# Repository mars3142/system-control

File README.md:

# System Control

See the [wiki](https://wiki.mars3142.dev/project/maerklin/system_control/start) for more information.

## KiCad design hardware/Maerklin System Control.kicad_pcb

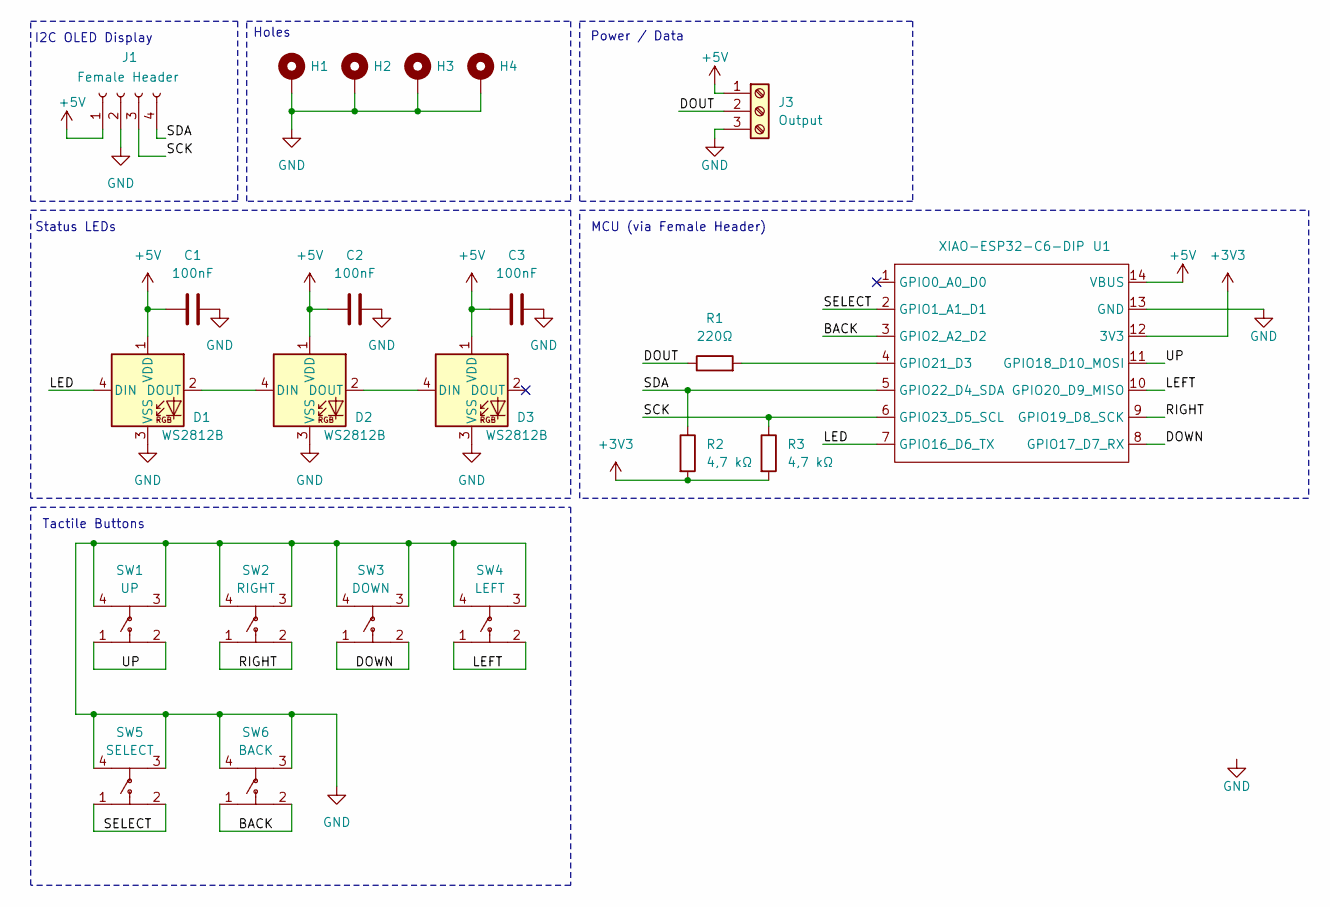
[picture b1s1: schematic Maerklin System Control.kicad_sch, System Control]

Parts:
C1, C2, C3: 100nF; C_0805_2012Metric_Pad1.18x1.45mm_HandSolder; LCSC C1711
D1, D2, D3: WS2812B; LED_WS2812B_PLCC4_5.0x5.0mm_P3.2mm; LCSC C22371521
H1: MH1; MountingHole_2.2mm_M2_Pad_Via
H2: MH2; MountingHole_2.2mm_M2_Pad_Via
H3: MH3; MountingHole_2.2mm_M2_Pad_Via
H4: MH4; MountingHole_2.2mm_M2_Pad_Via
J1: Female Header; PinSocket_1x04_P2.54mm_Horizontal; LCSC C5116530
J3: Output; TerminalBlock_Phoenix_MKDS-1,5-3_1x03_P5.00mm_Horizontal; LCSC Part C5188435
R1: 220Ω; R_0805_2012Metric_Pad1.20x1.40mm_HandSolder
R2, R3: 4,7 kΩ; R_0805_2012Metric_Pad1.20x1.40mm_HandSolder
SW1: UP; KEY-TH_4P-L6.0-W6.0-P3.90-LS7.8; LCSC Part C83205
SW2: RIGHT; KEY-TH_4P-L6.0-W6.0-P3.90-LS7.8; LCSC Part C83205
SW3: DOWN; KEY-TH_4P-L6.0-W6.0-P3.90-LS7.8; LCSC Part C83205
SW4: LEFT; KEY-TH_4P-L6.0-W6.0-P3.90-LS7.8; LCSC C83205
SW5: SELECT; KEY-TH_4P-L6.0-W6.0-P3.90-LS7.8; LCSC Part C83205
SW6: BACK; KEY-TH_4P-L6.0-W6.0-P3.90-LS7.8; LCSC Part C83205
U1: XIAO-ESP32-C6-DIP

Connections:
+3V3: R2.2, R3.2, U1.12 (3V3)
+5V: C1.1, C2.1, C3.1, D1.1 (VDD), D2.1 (VDD), D3.1 (VDD), J1.1, J3.1, U1.14 (VBUS)
/BACK: SW6.1, SW6.2, U1.3 (GPIO2_A2_D2)
/DOUT: J3.2, R1.1
/DOWN: SW3.1, SW3.2, U1.8 (GPIO17_D7_RX)
/LED: D1.4 (DIN), U1.7 (GPIO16_D6_TX)
/LEFT: SW4.1, SW4.2, U1.10 (GPIO20_D9_MISO)
/RIGHT: SW2.1, SW2.2, U1.9 (GPIO19_D8_SCK)
/SCK: J1.3, R3.1, U1.6 (GPIO23_D5_SCL)
/SDA: J1.4, R2.1, U1.5 (GPIO22_D4_SDA)
/SELECT: SW5.1, SW5.2, U1.2 (GPIO1_A1_D1)
/UP: SW1.1, SW1.2, U1.11 (GPIO18_D10_MOSI)
GND: C1.2, C2.2, C3.2, D1.3 (VSS), D2.3 (VSS), D3.3 (VSS), H1.1 (1_1), H2.1 (1_1), H3.1 (1_1), H4.1 (1_1), J1.2, J3.3, SW1.3, SW1.4, SW2.3, SW2.4, SW3.3, SW3.4, SW4.3, SW4.4, SW5.3, SW5.4, SW6.3, SW6.4, U1.13 (GND)
unnamed: D1.2 (DOUT), D2.4 (DIN)
unnamed: D2.2 (DOUT), D3.4 (DIN)
unnamed: R1.2, U1.4 (GPIO21_D3)

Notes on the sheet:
MCU (via Female Header)
Holes
Power / Data
Status LEDs
Tactile Buttons
I2C OLED Display

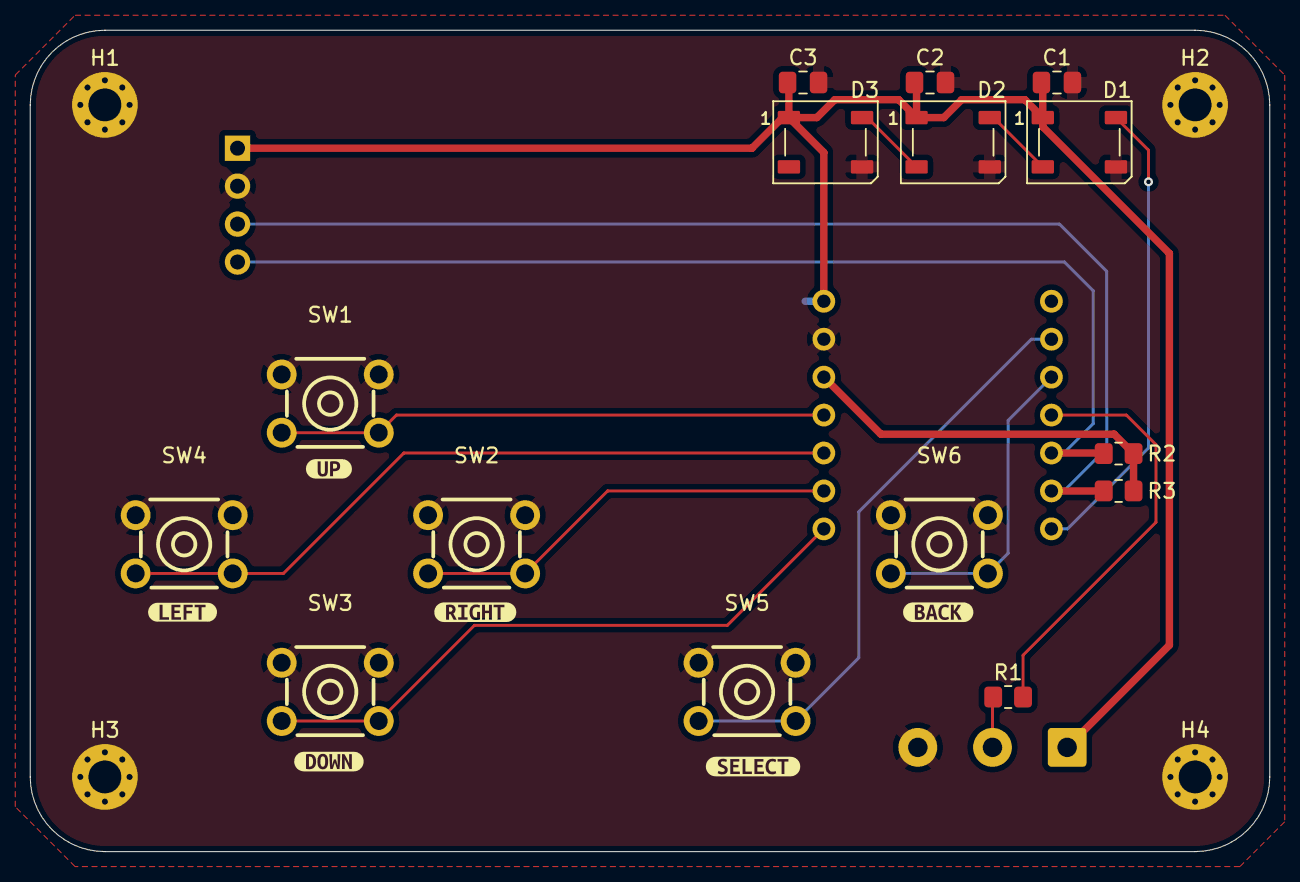
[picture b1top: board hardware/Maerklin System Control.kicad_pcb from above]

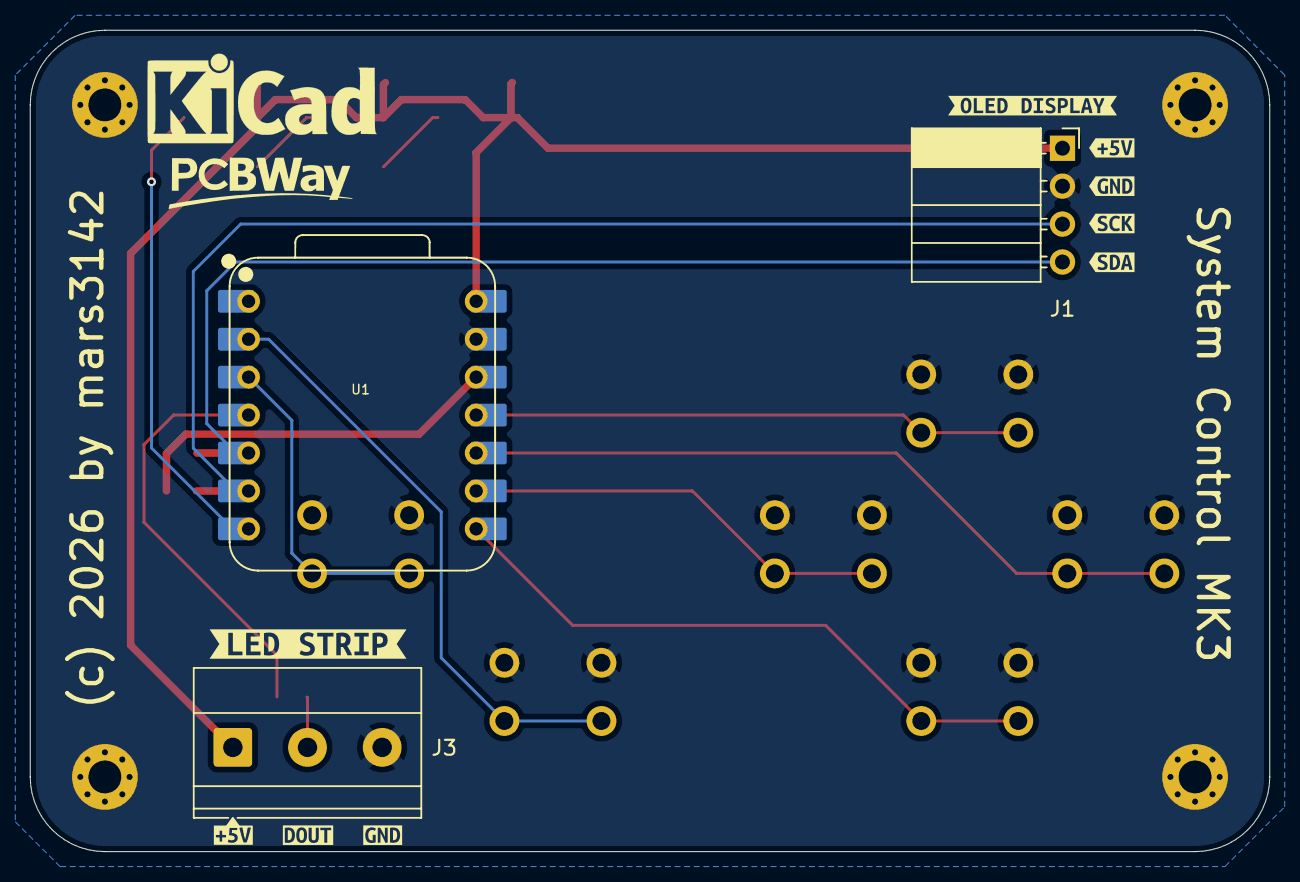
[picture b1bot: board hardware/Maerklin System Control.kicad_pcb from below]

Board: 2 copper layers, 83.0 x 55.0 mm, 37 parts (12 on the bottom side), 16 nets.

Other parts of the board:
kibuzzard-68D2E6D4: G***; kibuzzard-68D2E6D4
kibuzzard-68D2E6E4: G***; kibuzzard-68D2E6E4
kibuzzard-68D2E6EB: G***; kibuzzard-68D2E6EB
kibuzzard-68D2E6F2: G***; kibuzzard-68D2E6F2
kibuzzard-678A1323: G***; kibuzzard-678A1323
kibuzzard-6859B258: G***; kibuzzard-6859B258
kibuzzard-678980E8: G***; kibuzzard-678980E8
kibuzzard-678980F4: G***; kibuzzard-678980F4
kibuzzard-678981DB: G***; kibuzzard-678981DB
kibuzzard-678981FB: G***; kibuzzard-678981FB
kibuzzard-67898102: G***; kibuzzard-67898102
kibuzzard-67898208: G***; kibuzzard-67898208
kibuzzard-67898217: G***; kibuzzard-67898217
kibuzzard-67898221: G***; kibuzzard-67898221
kibuzzard-67898229: G***; kibuzzard-67898229

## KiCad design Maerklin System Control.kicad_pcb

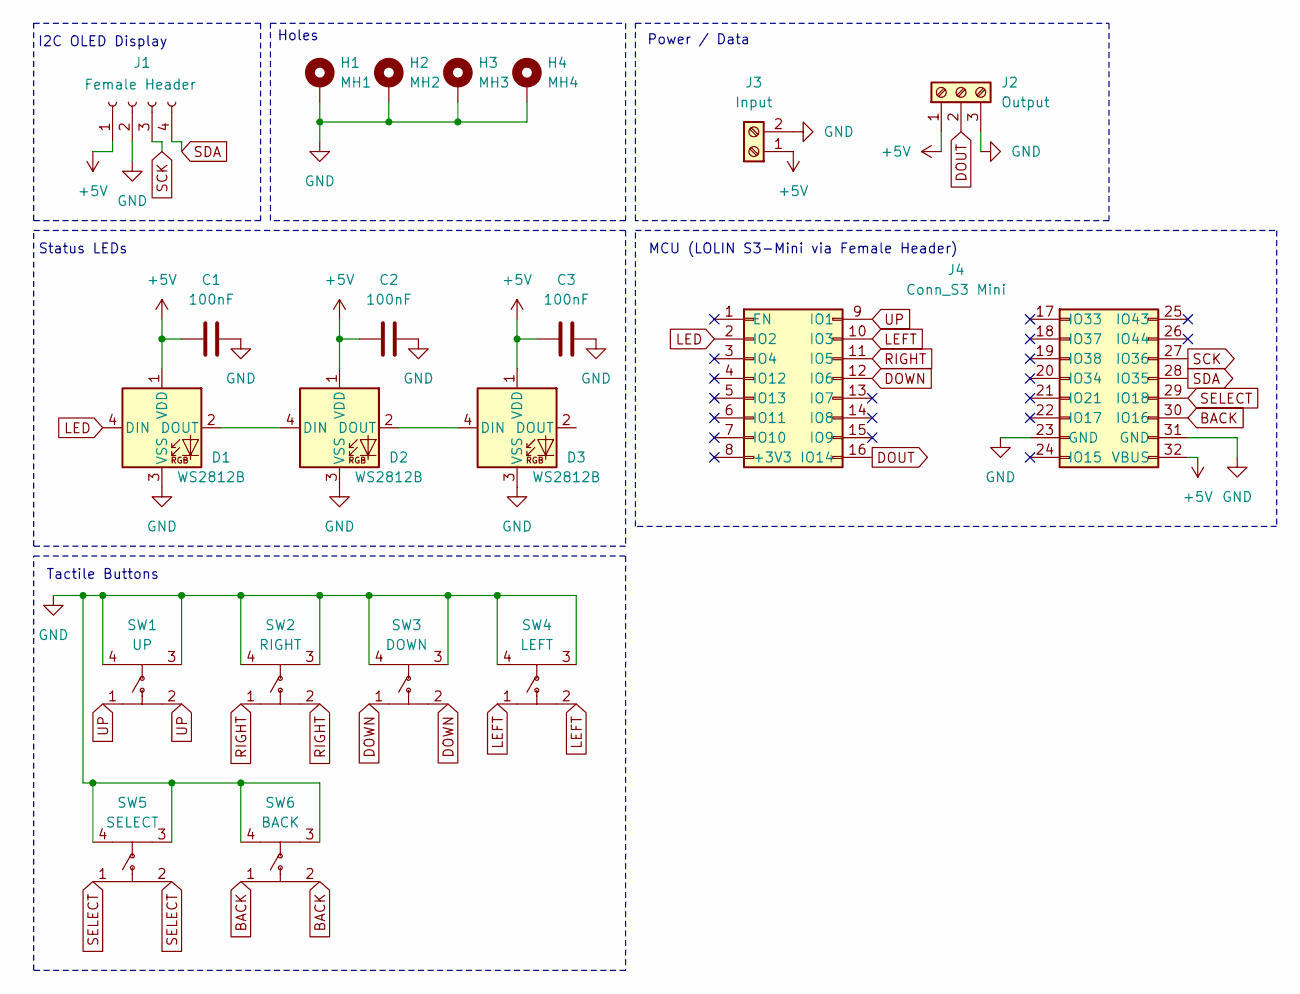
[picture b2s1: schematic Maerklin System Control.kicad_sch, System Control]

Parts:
C1, C2, C3: 100nF; C_0805_2012Metric_Pad1.18x1.45mm_HandSolder; LCSC C1711
D1, D2, D3: WS2812B; LED_WS2812B_PLCC4_5.0x5.0mm_P3.2mm; LCSC C22371521
H1: MH1; MountingHole_2.2mm_M2_Pad_Via
H2: MH2; MountingHole_2.2mm_M2_Pad_Via
H3: MH3; MountingHole_2.2mm_M2_Pad_Via
H4: MH4; MountingHole_2.2mm_M2_Pad_Via
J1: Female Header; PinSocket_1x04_P2.54mm_Vertical; LCSC C5116530
J2: Output; TerminalBlock_Phoenix_MKDS-1,5-3_1x03_P5.00mm_Horizontal; LCSC Part C5188435
J3: Input; TerminalBlock_Phoenix_MKDS-1,5-2_1x02_P5.00mm_Horizontal; LCSC Part C5188434
J4: Conn_S3 Mini; PinSocket_S3 Mini; LCSC Part C18722935
SW1: UP; KEY-TH_4P-L6.0-W6.0-P3.90-LS7.8; LCSC Part C83205
SW2: RIGHT; KEY-TH_4P-L6.0-W6.0-P3.90-LS7.8; LCSC Part C83205
SW3: DOWN; KEY-TH_4P-L6.0-W6.0-P3.90-LS7.8; LCSC Part C83205
SW4: LEFT; KEY-TH_4P-L6.0-W6.0-P3.90-LS7.8; LCSC C83205
SW5: SELECT; KEY-TH_4P-L6.0-W6.0-P3.90-LS7.8; LCSC Part C83205
SW6: BACK; KEY-TH_4P-L6.0-W6.0-P3.90-LS7.8; LCSC Part C83205

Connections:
+5V: C1.1, C2.1, C3.1, D1.1 (VDD), D2.1 (VDD), D3.1 (VDD), J1.1, J2.1, J3.1, J4.32 (VBUS)
BACK: J4.30 (IO16), SW6.1, SW6.2
DOUT: J2.2, J4.16 (IO14)
DOWN: J4.12 (IO6), SW3.1, SW3.2
GND: C1.2, C2.2, C3.2, D1.3 (VSS), D2.3 (VSS), D3.3 (VSS), H1.1, H2.1, H3.1, H4.1, J1.2, J2.3, J3.2, J4.23 (GND), J4.31 (GND), SW1.3, SW1.4, SW2.3, SW2.4, SW3.3, SW3.4, SW4.3, SW4.4, SW5.3, SW5.4, SW6.3, SW6.4
LED: D1.4 (DIN), J4.2 (IO2)
LEFT: J4.10 (IO3), SW4.1, SW4.2
unnamed: D1.2 (DOUT), D2.4 (DIN)
unnamed: D2.2 (DOUT), D3.4 (DIN)
RIGHT: J4.11 (IO5), SW2.1, SW2.2
SCK: J1.3, J4.27 (IO36)
SDA: J1.4, J4.28 (IO35)
SELECT: J4.29 (IO18), SW5.1, SW5.2
UP: J4.9 (IO1), SW1.1, SW1.2

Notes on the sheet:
MCU (LOLIN S3-Mini via Female Header)
Holes
Power / Data
Status LEDs
Tactile Buttons
I2C OLED Display

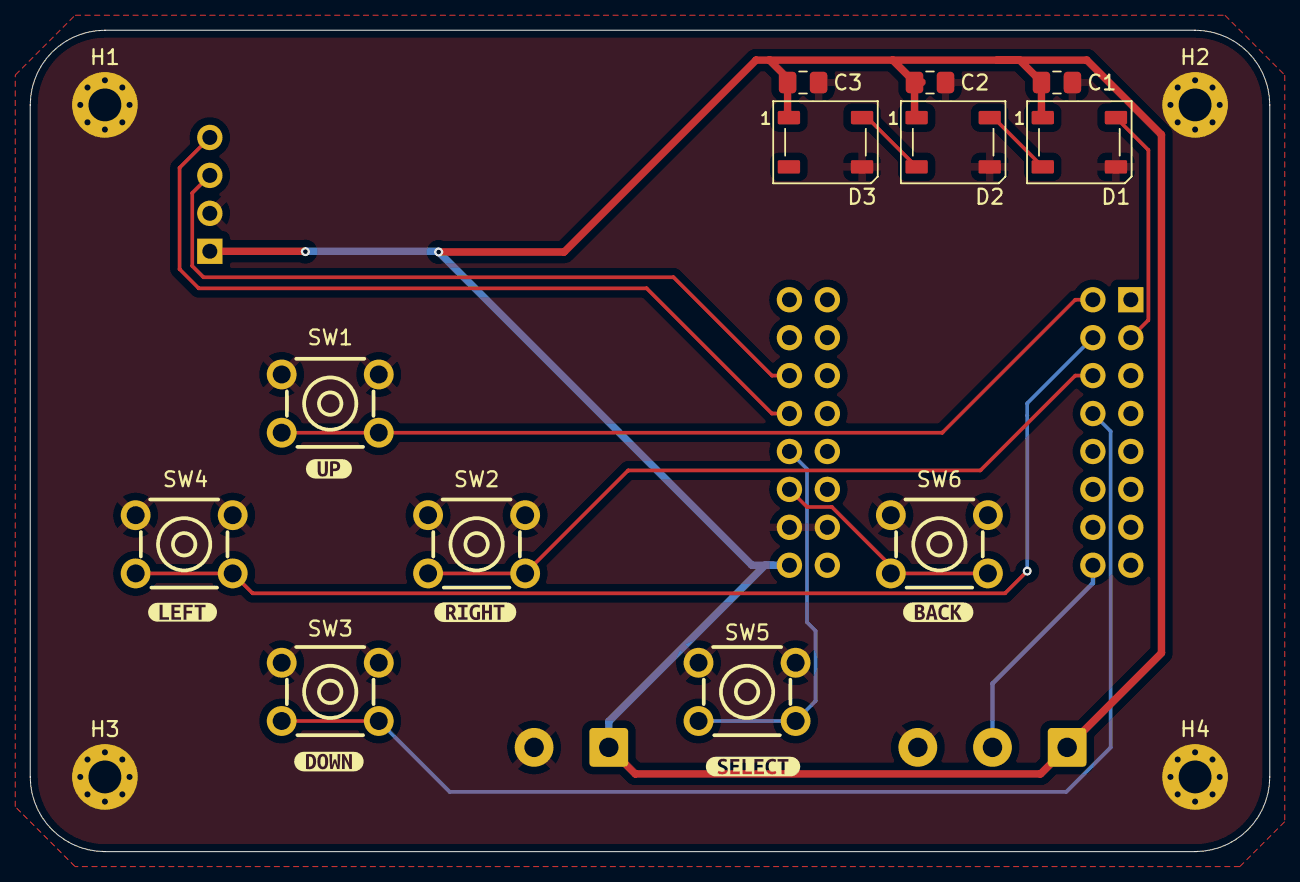
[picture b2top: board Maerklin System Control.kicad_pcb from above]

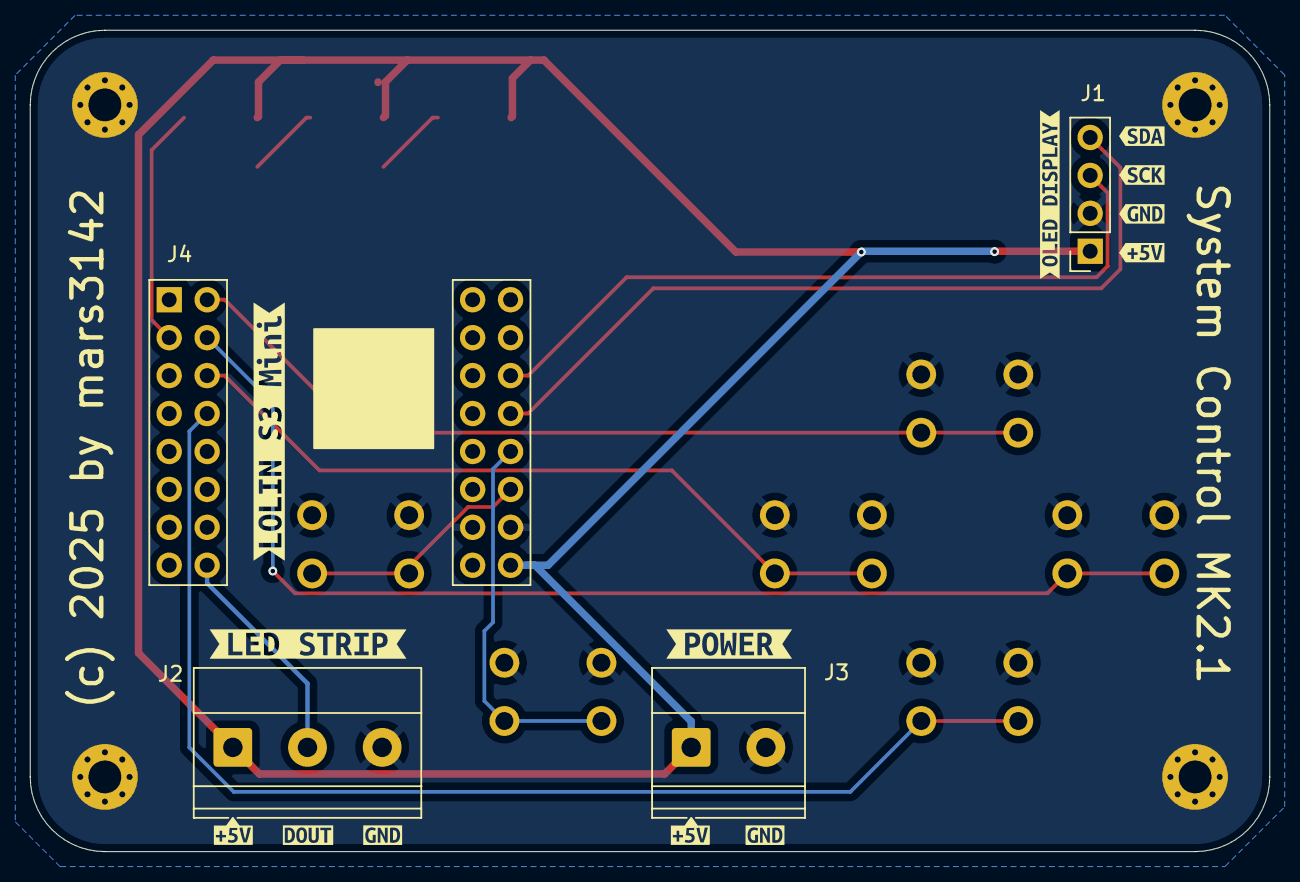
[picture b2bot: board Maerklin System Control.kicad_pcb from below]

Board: 2 copper layers, 83.0 x 55.0 mm, 39 parts (17 on the bottom side), 14 nets.

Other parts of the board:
kibuzzard-678A131B: G***; kibuzzard-678A131B
kibuzzard-678A1323: G***; kibuzzard-678A1323
kibuzzard-678A1332: G***; kibuzzard-678A1332
kibuzzard-6859B258: G***; kibuzzard-6859B258
kibuzzard-67897FC0: G***; kibuzzard-67897FC0
kibuzzard-678980A4: G***; kibuzzard-678980A4
kibuzzard-678980E8: G***; kibuzzard-678980E8
kibuzzard-678980F4: G***; kibuzzard-678980F4
kibuzzard-678981DB: G***; kibuzzard-678981DB
kibuzzard-678981FB: G***; kibuzzard-678981FB
kibuzzard-67898040: G***; kibuzzard-67898040
kibuzzard-67898062: G***; kibuzzard-67898062
kibuzzard-67898074: G***; kibuzzard-67898074
kibuzzard-67898084: G***; kibuzzard-67898084
kibuzzard-67898102: G***; kibuzzard-67898102
kibuzzard-67898208: G***; kibuzzard-67898208
kibuzzard-67898217: G***; kibuzzard-67898217
kibuzzard-67898221: G***; kibuzzard-67898221
kibuzzard-67898229: G***; kibuzzard-67898229

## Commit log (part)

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2025-04-10 removed lvgl references
2025-04-10 add cmake to .gitignore
2025-04-10 reduce default log level
2025-04-10 project file splitting
2025-04-10 combine with desktop project
2025-04-10 desktop code refactoring
2025-04-11 more modules for the MCU code
2025-04-11 more gitignore
2025-04-11 fixing format error
2025-04-11 custom bootloader code and starting app as task
2025-04-18 fixed u8g2 checkout for desktop (hopefully)
2025-04-18 add action permissions
2025-04-18 add missing include
2025-06-08 handle mouse events
2025-06-09 implement onTap and remove memory leaks
2025-06-12 some more widgets
2025-06-12 restructure folder
2025-06-12 only latest stable ESP-IDF and "latest"
2025-06-12 pin u8g2 to specific version for ESP-IDF
    see https://github.com/olikraus/u8g2/issues/2658
2025-06-14 optimized and commented code
2025-06-14 implement left/right with callback
2025-06-14 starting convert for ESP32
2025-06-15 more interaction
2025-06-15 scrollbar optimization
2025-06-15 more callback functions
2025-06-15 starting MCU development
2025-06-15 added check for ESP32H2
2025-06-15 latest ImGui
2025-06-15 latest u8g2 package
2025-06-15 showing the menu on the MCU display
2025-06-16 dummy pins for compile checks
2025-06-17 reduce startup time on ESP32
2025-06-19 add screensaver and optimize performance
2025-06-20 implement ScreenSaver in simulator
    set ruth to stub only, because of cross compile error
2025-06-20 code optimization
    - lifecycle functions for widgets
    - persistence functions
2025-06-20 more comments
2025-06-20 code cleanup
2025-06-20 checking persistence on desktop and esp32
2025-06-20 move PersistenceManager into platform project
2025-06-21 starting with led-manager as esp32 and native component
2025-06-22 new native matrix implementation
2025-06-23 new persistence manager component
2025-06-24 new Screensaver
2025-06-25 increase timeout time for screensaver
2025-06-25 auto load and dependency fix
2025-06-26 better spawn delay for ESP32
2025-06-27 use button component from espressif
2025-07-01 add submodule
2025-07-01 start with v1.2
2025-07-01 RC of mk2
2025-07-01 remove datasheets
2025-07-01 latest submodule version
2025-07-01 use of external library
2025-07-01 update library
2025-07-01 latest design
2025-07-01 latest v1.1 iteration
2025-07-01 latest library
2025-07-03 latest corrections
2025-07-18 FIX: WLED connection
2025-07-22 update sheet comments
2025-07-26 updated esp-idf version in github action
2025-08-20 move into firmware subfolder
2025-08-20 move into hardware subfolder
2025-08-20 added README.md
2025-08-21 add new ClockScreenSaver
2025-08-21 update submodule link
2025-08-21 fix action
2025-08-23 fix link for kicad library
2025-08-23 starting status WLEDs behavior
2025-08-23 folder cleanup
2025-08-29 scan ble advertise packages
2025-09-11 add i2c check for display
2025-09-11 partition change (for future FOTAs)
2025-09-11 remove desktop build (for now)
2025-09-11 more kconfig options
2025-09-11 connect via wifi and enable esp insights
2025-09-12 optimize ESP Insights handling
2025-09-12 add other esp insights log types
2025-09-13 optimize init sequenze
    show SplashScreen while connecting
2025-09-13 new partition table
2025-09-13 fix compile error
2025-09-13 new color schema and intervals for status led
2025-09-13 optimize some log entries
2025-09-20 latest hardware lib
2025-09-20 some optimizations regarding LED color
2025-09-20 add sponsoring
2025-09-26 day/night cycle on LED 1 from CSV file
2025-09-26 autogeneration of wiki files (schematics and PCB screenshots)
2025-09-26 switch from global net labels to local
2025-09-29 implement new light mode (off/day/night/simulation)
    missing:
    - fully connect it to the ui
    - setup duration in light settings
2025-09-30 optimise simulation handling
2025-09-30 new light schema file
2025-09-30 add simulation to UI
2025-10-01 fix github action
2025-10-01 extract API key
2025-10-01 move actions to gitea only
2025-12-20 fix analytics key file name
2025-12-20 debugging action
2025-12-20 better path
2025-12-20 esp-idf build
2025-12-20 more optimisation
2025-12-20 remove container in container
2025-12-20 manual git checkout
2025-12-20 external MQTT component
2025-12-20 use defined release branches
2025-12-20 add external package
2025-12-20 disable external devices
2025-12-20 remove ESP-IDF v6
2025-12-23 MK 2.1 of the System Control (ESP32-S3)
2025-12-24 show NTP time while day/night - and "simulated" while simulation
2025-12-24 fix crash
2025-12-24 disable BLE scan at startup
    we will refactor it to Thread later
2025-12-24 fix imports
2025-12-25 multiple wifi connection for login check
2025-12-26 send button event to ESP Insights
2025-12-26 fix I2C timeout crash
2025-12-26 send screen names to ESP Insights
2025-12-26 version bump
2026-01-01 vibe coded website (plus captive portal)
    needs missing ESP32 implementation
2026-01-01 add segment settings
2026-01-01 rename WLED to LED
2026-01-01 hide thread configuration (for now)
2026-01-01 add thunder configuration
2026-01-05 show website via mdns
2026-01-05 scan for WiFi and schon connection state (loading once)
2026-01-05 add capa endpoint
2026-01-05 mask password in log
2026-01-09 update web ui
2026-01-10 refactor persistence manager from cpp to c
2026-01-12 show capative portal on connect
2026-01-14 optimize AP mode
    - save wifi data
    - show status led
2026-01-18 implement reset via back button
2026-01-18 fixed devcontainer image
2026-01-18 shared website header
2026-01-18 light on/off via REST or GPIO
2026-01-18 rework message manager
    use of listener pattern instead of message queue
2026-01-18 refresh device ui after REST call
2026-01-18 send current state via WS
2026-01-18 change light mode
    day/night/simulation
2026-01-18 read schema files for website
2026-01-18 change schema via REST
2026-01-18 update comments
2026-01-18 more status values
2026-01-18 show correct schame on website
2026-01-18 update time on website via webSocket
2026-01-19 try to use react for SPA
    initial setup - no real function yet
2026-01-21 get/post led segments
2026-01-24 edit of all config data via website
2026-01-24 remove PSRAM usage
2026-01-25 connect via MQTTS
2026-01-25 rebuild websites with svelte
    still early WIP
2026-01-25 add ignore for FreeCAD and node-js intermediate files
2026-01-25 add vite helper files?
2026-02-06 preparation for switch to C6 MCU (but also compatible with S3)
2026-03-16 website in svelte
2026-03-16 try to fix action
2026-03-16 some website tweeks
2026-03-16 ESP32 C6 support
2026-03-16 code enhancements
    - add MQTT
    - add ESP32-C6
    - fix simulation
2026-03-16 fix null termination
2026-03-17 latest website and FW changes
2026-03-17 optimize refreshes and add AI agent helper
2026-03-21 latest website
2026-03-21 convert to svelte 5
2026-03-23 latest kicad data
2026-03-23 updated firmware code
2026-03-23 captive is plain html (no svelte)
2026-03-23 Auto-commited changes
2026-03-25 updated captive portal
2026-03-25 latest KiCad format
2026-03-26 Bump picomatch from 2.3.1 to 2.3.2 in /firmware/website
    Bumps [picomatch](https://github.com/micromatch/picomatch) from 2.3.1 to 2.3.2.
    - [Release notes](https://github.com/micromatch/picomatch/releases)
    - [Changelog](https://github.com/micromatch/picomatch/blob/master/CHANGELOG.md)
    - [Commits](https://github.com/micromatch/picomatch/compare/2.3.1...2.3.2)
    ---
    updated-dependencies:
2026-03-28 starting data driven (dynamic) menu
2026-03-28 dynamic menu
    - also component renaming
2026-03-28 documentation for menu.json
2026-03-28 remove ESP Insights
2026-03-29 add Claude instructions
2026-03-29 testing OpenThread
2026-04-06 Bump vite from 7.3.1 to 7.3.2 in /firmware/website
    Bumps [vite](https://github.com/vitejs/vite/tree/HEAD/packages/vite) from 7.3.1 to 7.3.2.
    - [Release notes](https://github.com/vitejs/vite/releases)
    - [Changelog](https://github.com/vitejs/vite/blob/v7.3.2/packages/vite/CHANGELOG.md)
    - [Commits](https://github.com/vitejs/vite/commits/v7.3.2/packages/vite)
    ---
    updated-dependencies:
2026-04-07 latest website iteration (including FW code fixes for it)
2026-04-17 starting matter over thread
2026-04-18 Add renovate.json
2026-04-19 Update dependency @sveltejs/vite-plugin-svelte to v7
2026-04-19 Update dependency svelte-spa-router to v5
2026-04-19 Update dependency tailwindcss to v4
2026-04-19 Update dependency vite to v8
2026-04-20 Update dependency vitest to v4
2026-04-24 switch to tailwind v4
2026-05-08 remove unused insa (UI) component
2026-05-08 testing thread
    - remove BLE
    - remove MQTT
2026-05-14 Bump devalue from 5.6.4 to 5.8.1 in /firmware/website
    Bumps [devalue](https://github.com/sveltejs/devalue) from 5.6.4 to 5.8.1.
    - [Release notes](https://github.com/sveltejs/devalue/releases)
    - [Changelog](https://github.com/sveltejs/devalue/blob/main/CHANGELOG.md)
    - [Commits](https://github.com/sveltejs/devalue/compare/v5.6.4...v5.8.1)
    ---
    updated-dependencies:
2026-05-14 Bump svelte from 5.55.4 to 5.55.7 in /firmware/website
    Bumps [svelte](https://github.com/sveltejs/svelte/tree/HEAD/packages/svelte) from 5.55.4 to 5.55.7.
    - [Release notes](https://github.com/sveltejs/svelte/releases)
    - [Changelog](https://github.com/sveltejs/svelte/blob/main/packages/svelte/CHANGELOG.md)
    - [Commits](https://github.com/sveltejs/svelte/commits/svelte@5.55.7/packages/svelte)
    ---
    updated-dependencies:
2026-05-31 Bump svelte from 5.55.4 to 5.56.0 in /firmware/website
    Bumps [svelte](https://github.com/sveltejs/svelte/tree/HEAD/packages/svelte) from 5.55.4 to 5.56.0.
    - [Release notes](https://github.com/sveltejs/svelte/releases)
    - [Changelog](https://github.com/sveltejs/svelte/blob/main/packages/svelte/CHANGELOG.md)
    - [Commits](https://github.com/sveltejs/svelte/commits/svelte@5.56.0/packages/svelte)
    ---
    updated-dependencies:
2026-06-01 Bump vitest from 3.2.4 to 4.1.0 in /firmware/website
    Bumps [vitest](https://github.com/vitest-dev/vitest/tree/HEAD/packages/vitest) from 3.2.4 to 4.1.0.
    - [Release notes](https://github.com/vitest-dev/vitest/releases)
    - [Changelog](https://github.com/vitest-dev/vitest/blob/main/docs/releases.md)
    - [Commits](https://github.com/vitest-dev/vitest/commits/v4.1.0/packages/vitest)
    ---
    updated-dependencies:
2026-06-09 Bump vitest from 3.2.4 to 3.2.6 in /firmware/website
    Bumps [vitest](https://github.com/vitest-dev/vitest/tree/HEAD/packages/vitest) from 3.2.4 to 3.2.6.
    - [Release notes](https://github.com/vitest-dev/vitest/releases)
    - [Changelog](https://github.com/vitest-dev/vitest/blob/main/docs/releases.md)
    - [Commits](https://github.com/vitest-dev/vitest/commits/v3.2.6/packages/vitest)
    ---
    updated-dependencies:
2026-06-19 Bump vite, @sveltejs/vite-plugin-svelte and vitest in /firmware/website
    Bumps [vite](https://github.com/vitejs/vite/tree/HEAD/packages/vite), [@sveltejs/vite-plugin-svelte](https://github.com/sveltejs/vite-plugin-svelte/tree/HEAD/packages/vite-plugin-svelte) and [vitest]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
    Updates `vite` from 7.3.2 to 8.0.16
    - [Release notes](https://github.com/vitejs/vite/releases)
    - [Changelog](https://github.com/vitejs/vite/blob/main/packages/vite/CHANGELOG.md)
    - [Commits](https://github.com/vitejs/vite/commits/v8.0.16/packages/vite)
    Updates `@sveltejs/vite-plugin-svelte` from 6.2.4 to 7.1.2

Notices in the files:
Maerklin System Control.kicad_pcb:
(c) 2025 by mars3142
hardware/Maerklin System Control.kicad_pcb:
(c) 2026 by mars3142
